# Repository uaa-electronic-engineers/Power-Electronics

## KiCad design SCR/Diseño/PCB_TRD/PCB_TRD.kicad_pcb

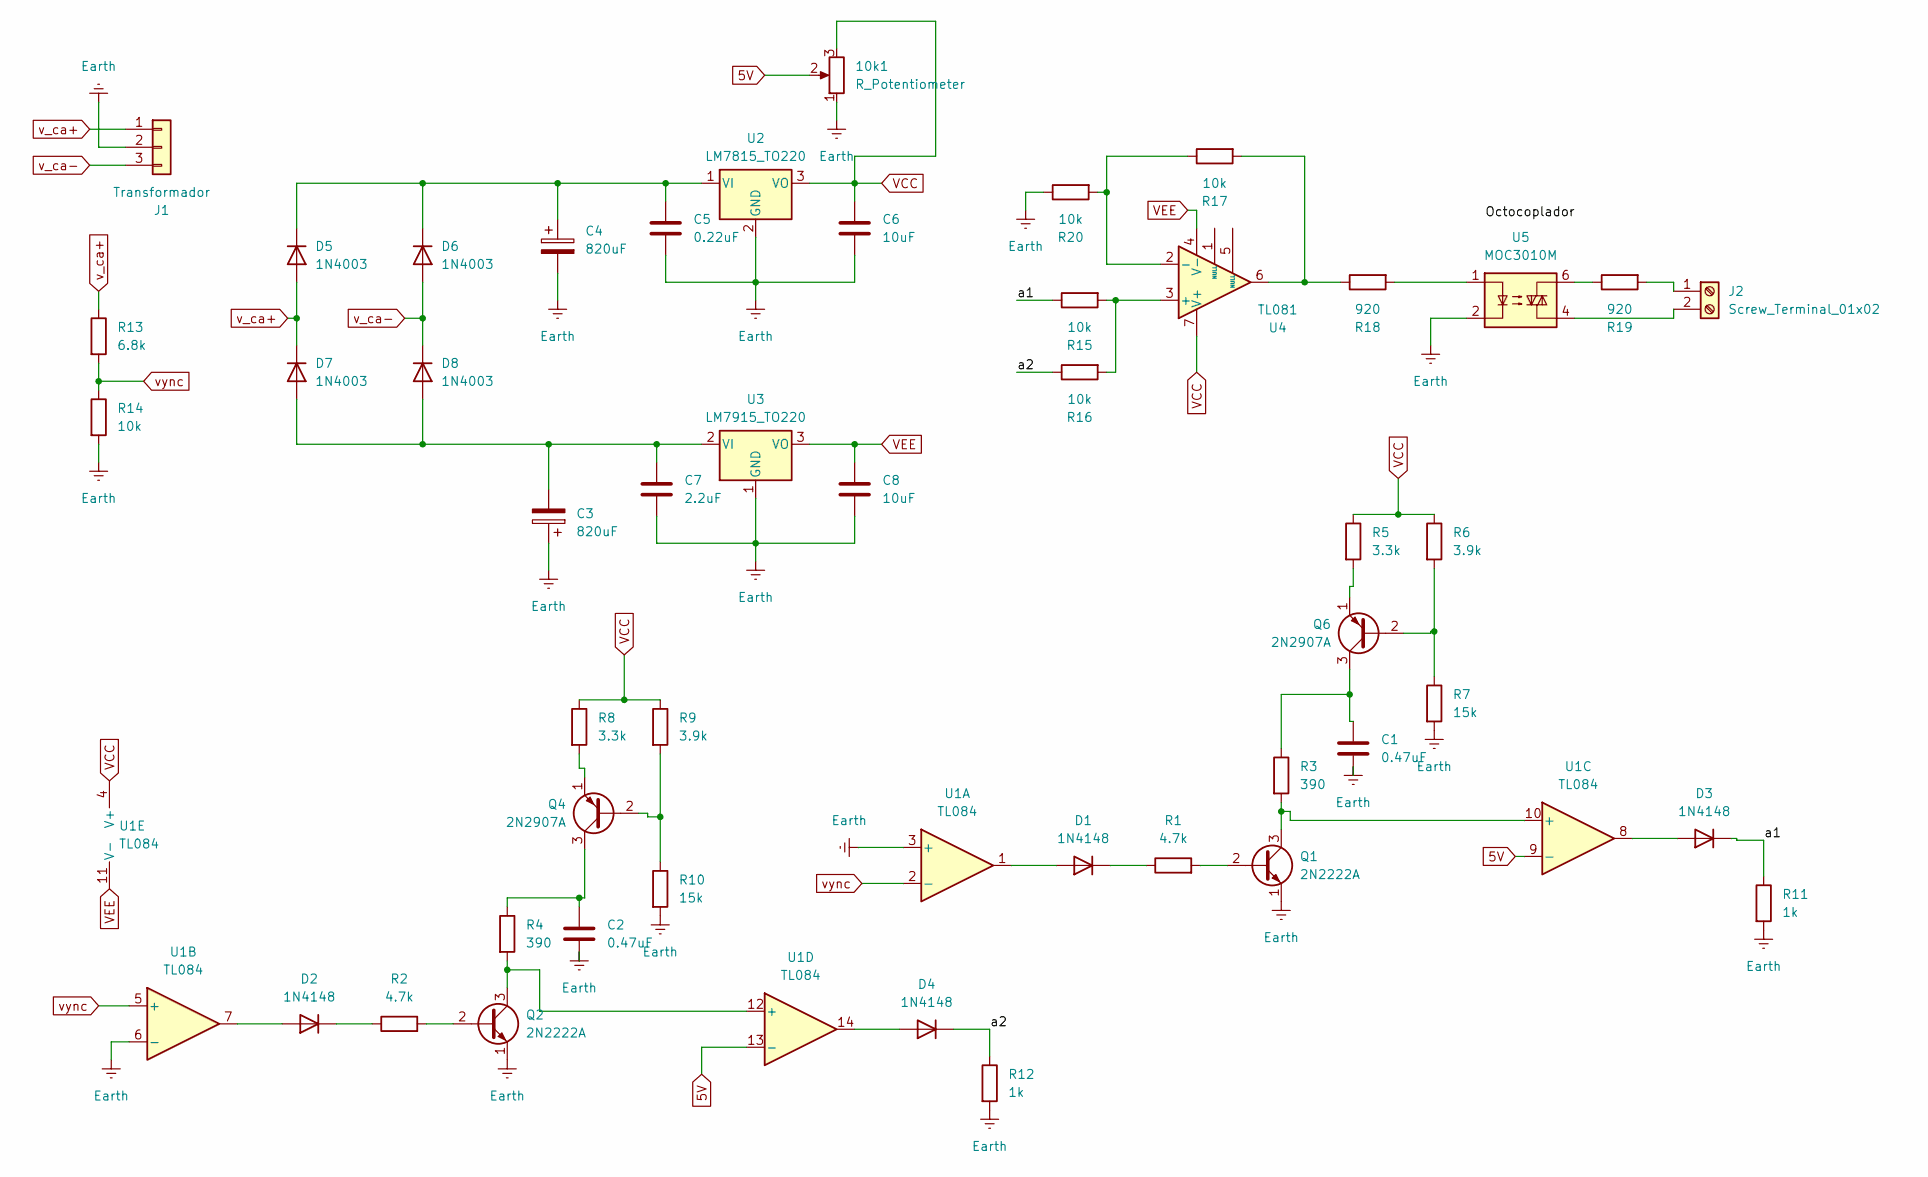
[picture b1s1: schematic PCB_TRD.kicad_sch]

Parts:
10k1: R_Potentiometer; Potentiometer_Alps_RK163_Single_Horizontal
C1, C2: 0.47uF; CP_Radial_D5.0mm_P2.50mm
C3, C4: 820uF; CP_Radial_D10.0mm_P5.00mm
C5: 0.22uF; C_Disc_D5.0mm_W2.5mm_P2.50mm
C6, C8: 10uF; CP_Radial_D5.0mm_P2.50mm
C7: 2.2uF; C_Disc_D10.0mm_W2.5mm_P5.00mm
D1, D2, D3, D4: 1N4148; D_DO-35_SOD27_P7.62mm_Horizontal
D5, D6, D7, D8: 1N4003; D_DO-41_SOD81_P10.16mm_Horizontal
J1: Transformador; TerminalBlock_MaiXu_MX126-5.0-03P_1x03_P5.00mm
J2: Screw_Terminal_01x02; TerminalBlock_MaiXu_MX126-5.0-02P_1x02_P5.00mm
Q1, Q2: 2N2222A; TO-92L_Inline_Wide
Q4, Q6: 2N2907A; TO-92L_Inline_Wide
R1, R2: 4.7k; R_Axial_DIN0411_L9.9mm_D3.6mm_P5.08mm_Vertical
R3, R4: 390; R_Axial_DIN0411_L9.9mm_D3.6mm_P5.08mm_Vertical
R5, R8: 3.3k; R_Axial_DIN0411_L9.9mm_D3.6mm_P5.08mm_Vertical
R6, R9: 3.9k; R_Axial_DIN0411_L9.9mm_D3.6mm_P5.08mm_Vertical
R7, R10: 15k; R_Axial_DIN0411_L9.9mm_D3.6mm_P5.08mm_Vertical
R11, R12: 1k; R_Axial_DIN0411_L9.9mm_D3.6mm_P5.08mm_Vertical
R13: 6.8k; R_Axial_DIN0411_L9.9mm_D3.6mm_P5.08mm_Vertical
R14, R15, R16, R17, R20: 10k; R_Axial_DIN0411_L9.9mm_D3.6mm_P5.08mm_Vertical
R18, R19: 920; R_Axial_DIN0411_L9.9mm_D3.6mm_P5.08mm_Vertical
U1: TL084; DIP-14_W7.62mm_LongPads
U2: LM7815_TO220; TO-220-3_Vertical
U3: LM7915_TO220; TO-220-3_Vertical
U4: TL081; CERDIP-8_W7.62mm_SideBrazed_LongPads_Socket
U5: MOC3010M; DIP-6_W7.62mm_Socket_LongPads

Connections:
5V: 10k1.2, U1.9 (-), U1.13 (-)
/a1: D3.1 (K), R11.1, R15.1
/a2: D4.1 (K), R12.1, R16.1
Earth: 10k1.1, C1.2, C2.2, C3.1, C4.2, C5.2, C6.2, C7.2, C8.2, J1.2, Q1.1 (E), Q2.1 (E), R7.2, R10.2, R11.2, R12.2, R14.2, R20.1, U1.3 (+), U1.6 (-), U2.2 (GND), U3.1 (GND), U5.2
unnamed: D1.2 (A), U1.1
unnamed: D1.1 (K), R1.1
unnamed: D2.2 (A), U1.7
unnamed: D2.1 (K), R2.1
unnamed: D3.2 (A), U1.8
unnamed: D4.2 (A), U1.14
unnamed: C4.1, C5.1, D5.1 (K), D6.1 (K), U2.1 (VI)
unnamed: C3.2, C7.1, D7.2 (A), D8.2 (A), U3.2 (VI)
unnamed: J2.1, R19.2
unnamed: J2.2, U5.4
unnamed: Q1.2 (B), R1.2
unnamed: Q1.3 (C), R3.2, U1.10 (+)
unnamed: Q2.2 (B), R2.2
unnamed: Q2.3 (C), R4.2, U1.12 (+)
unnamed: Q4.2 (B), R9.2, R10.1
unnamed: C2.1, Q4.3 (C), R4.1
unnamed: Q4.1 (E), R8.2
unnamed: Q6.2 (B), R6.2, R7.1
unnamed: C1.1, Q6.3 (C), R3.1
unnamed: Q6.1 (E), R5.2
unnamed: R17.2, R18.1, U4.6
unnamed: R18.2, U5.1
unnamed: R19.1, U5.6
unnamed: R15.2, R16.2, U4.3 (+)
unnamed: R17.1, R20.2, U4.2 (-)
VCC: 10k1.3, C6.1, R5.1, R6.1, R8.1, R9.1, U1.4 (V+), U2.3 (VO), U4.7 (V+)
VEE: C8.1, U1.11 (V-), U3.3 (VO), U4.4 (V-)
v_ca+: D5.2 (A), D7.1 (K), J1.1, R13.1
v_ca-: D6.2 (A), D8.1 (K), J1.3
vync: R13.2, R14.1, U1.2 (-), U1.5 (+)

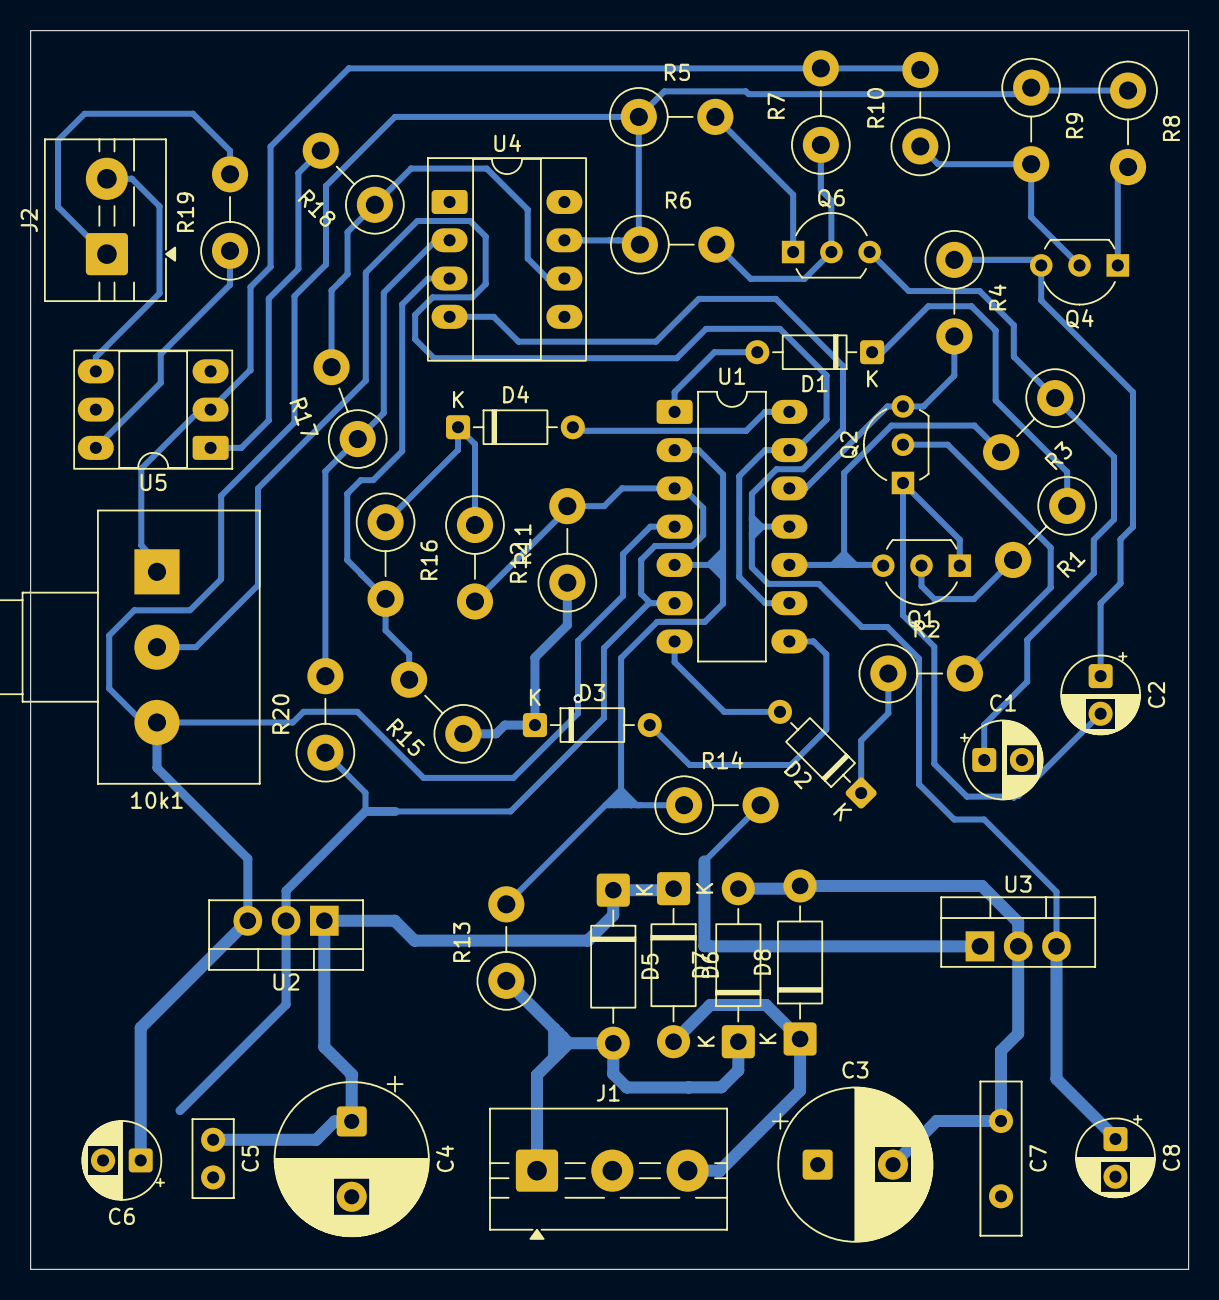
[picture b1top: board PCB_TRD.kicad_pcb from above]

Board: 2 copper layers, 76.9 x 82.2 mm, 48 parts (0 on the bottom side), 34 nets.
